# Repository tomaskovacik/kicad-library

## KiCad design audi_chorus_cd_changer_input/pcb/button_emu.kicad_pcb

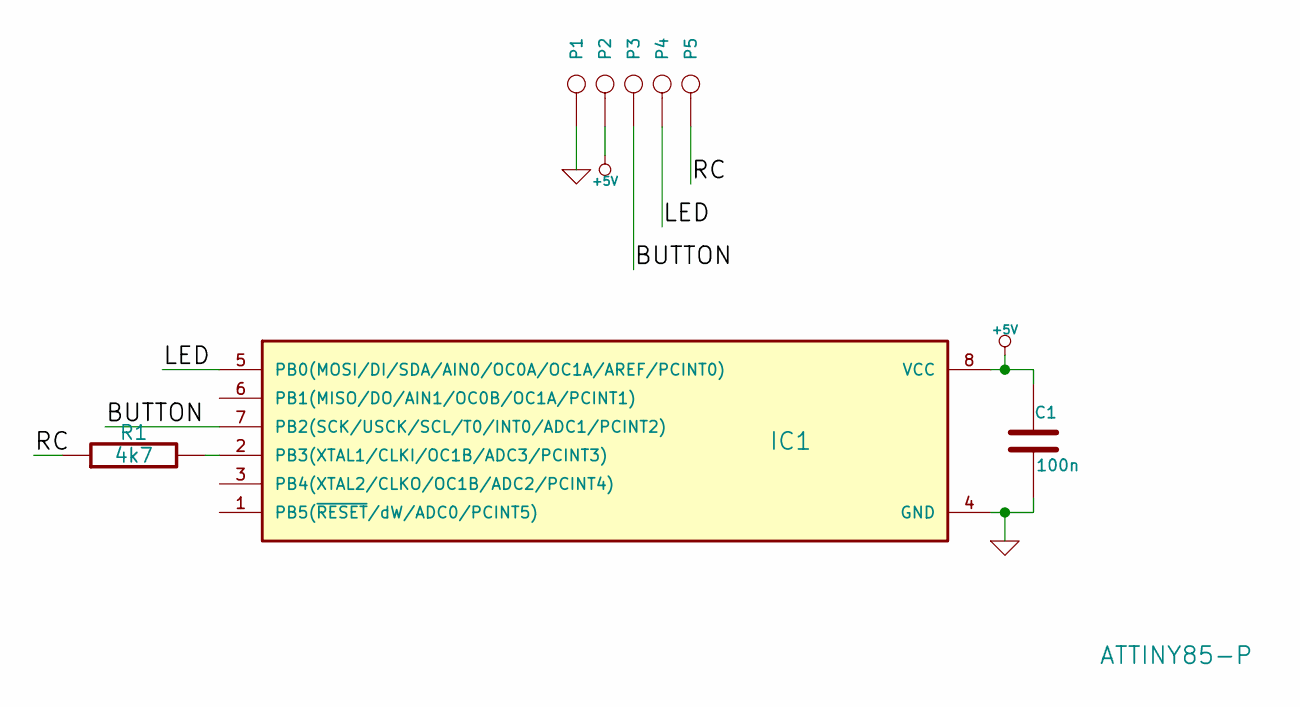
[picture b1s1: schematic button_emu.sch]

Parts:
C1: 100n
IC1: ATTINY85-P; DIP8
P1, P2, P3, P4, P5: CONN_1
R1: 4k7

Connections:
+5V: C1.1, IC1.8 (VCC), P2.1
/BUTTON: IC1.7 (PB2(SCK/USCK/SCL/T0/INT0/ADC1/PCINT2)), P3.1
/LED: IC1.5 (PB0(MOSI/DI/SDA/AIN0/OC0A/OC1A/AREF/PCI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), P4.1
/RC: P5.1, R1.1
GND: C1.2, IC1.4 (GND), P1.1
unnamed: IC1.2 (PB3(XTAL1/CLKI/OC1B/ADC3/PCINT3)), R1.2

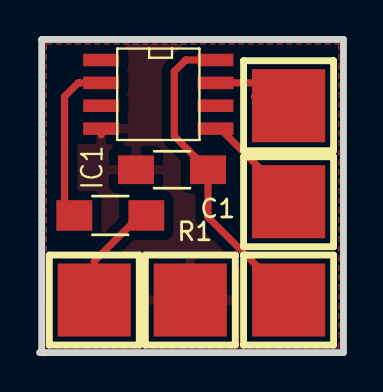
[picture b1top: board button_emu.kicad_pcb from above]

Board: 2 copper layers, 16.9 x 17.4 mm, 8 parts (0 on the bottom side), 6 nets.

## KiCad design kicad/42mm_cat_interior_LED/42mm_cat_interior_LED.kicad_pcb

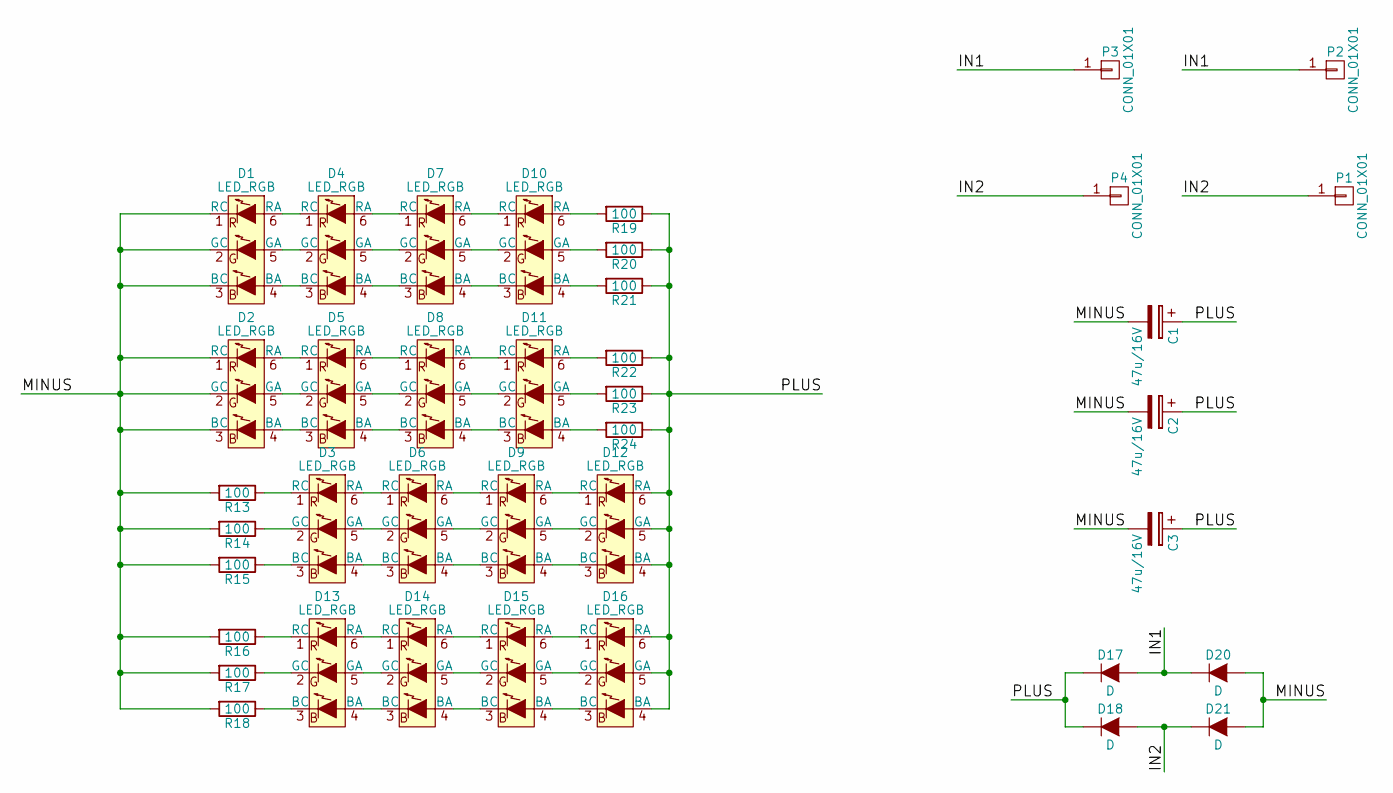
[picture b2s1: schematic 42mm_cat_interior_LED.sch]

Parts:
C1, C2, C3: 47u/16V; TantalC_SizeD_EIA-7343
D1, D2, D3, D4, D5, D6, D7, D8, D9, D10, D11, D12, D13, D14, D15, D16: LED_RGB; 5050_LED
D17, D18, D20, D21: D; DO-214AA
P1, P2, P3, P4: CONN_01X01; 1Pin
R13, R14, R15, R16, R17, R18, R19, R20, R21, R22, R23, R24: 100; R_1206

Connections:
/IN1: D17.2 (A), D20.1 (K), P2.1, P3.1
/IN2: D18.2 (A), D21.1 (K), P1.1, P4.1
/MINUS: C1.2, C2.2, C3.2, D1.1 (RC), D1.2 (GC), D1.3 (BC), D2.1 (RC), D2.2 (GC), D2.3 (BC), D20.2 (A), D21.2 (A), R13.2, R14.2, R15.2, R16.2, R17.2, R18.2
/PLUS: C1.1, C2.1, C3.1, D12.4 (BA), D12.5 (GA), D12.6 (RA), D16.4 (BA), D16.5 (GA), D16.6 (RA), D17.1 (K), D18.1 (K), R19.1, R20.1, R21.1, R22.1, R23.1, R24.1
unnamed: D1.4 (BA), D4.3 (BC)
unnamed: D1.5 (GA), D4.2 (GC)
unnamed: D1.6 (RA), D4.1 (RC)
unnamed: D2.4 (BA), D5.3 (BC)
unnamed: D2.5 (GA), D5.2 (GC)
unnamed: D2.6 (RA), D5.1 (RC)
unnamed: D3.1 (RC), R13.1
unnamed: D3.2 (GC), R14.1
unnamed: D3.3 (BC), R15.1
unnamed: D3.4 (BA), D6.3 (BC)
unnamed: D3.5 (GA), D6.2 (GC)
unnamed: D3.6 (RA), D6.1 (RC)
unnamed: D4.4 (BA), D7.3 (BC)
unnamed: D4.5 (GA), D7.2 (GC)
unnamed: D4.6 (RA), D7.1 (RC)
unnamed: D5.4 (BA), D8.3 (BC)
unnamed: D5.5 (GA), D8.2 (GC)
unnamed: D5.6 (RA), D8.1 (RC)
unnamed: D6.4 (BA), D9.3 (BC)
unnamed: D6.5 (GA), D9.2 (GC)
unnamed: D6.6 (RA), D9.1 (RC)
unnamed: D7.6 (RA), D10.1 (RC)
unnamed: D7.5 (GA), D10.2 (GC)
unnamed: D7.4 (BA), D10.3 (BC)
unnamed: D10.4 (BA), R21.2
unnamed: D10.5 (GA), R20.2
unnamed: D10.6 (RA), R19.2
unnamed: D8.6 (RA), D11.1 (RC)
unnamed: D8.5 (GA), D11.2 (GC)
unnamed: D8.4 (BA), D11.3 (BC)
unnamed: D11.4 (BA), R24.2
unnamed: D11.5 (GA), R23.2
unnamed: D11.6 (RA), R22.2
unnamed: D9.6 (RA), D12.1 (RC)
unnamed: D9.5 (GA), D12.2 (GC)
unnamed: D9.4 (BA), D12.3 (BC)
unnamed: D13.1 (RC), R16.1
unnamed: D13.2 (GC), R17.1
unnamed: D13.3 (BC), R18.1
unnamed: D13.4 (BA), D14.3 (BC)
unnamed: D13.5 (GA), D14.2 (GC)
unnamed: D13.6 (RA), D14.1 (RC)
unnamed: D14.4 (BA), D15.3 (BC)
unnamed: D14.5 (GA), D15.2 (GC)
unnamed: D14.6 (RA), D15.1 (RC)
unnamed: D15.4 (BA), D16.3 (BC)
unnamed: D15.5 (GA), D16.2 (GC)
unnamed: D15.6 (RA), D16.1 (RC)

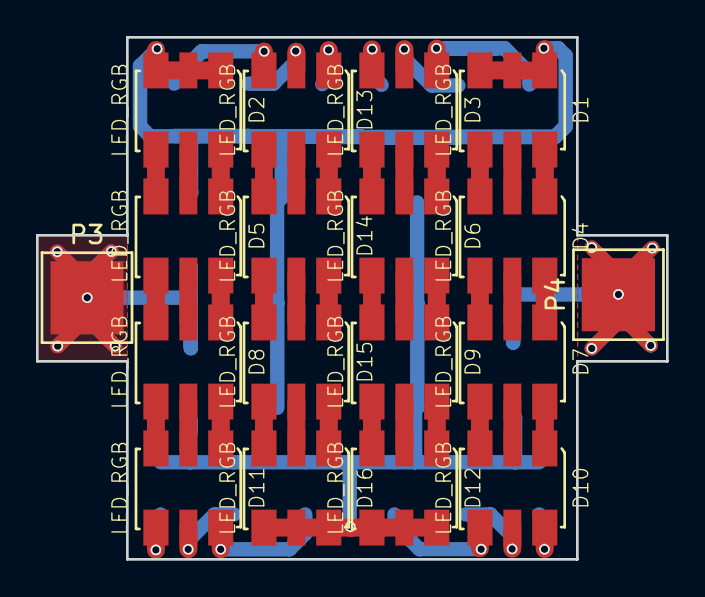
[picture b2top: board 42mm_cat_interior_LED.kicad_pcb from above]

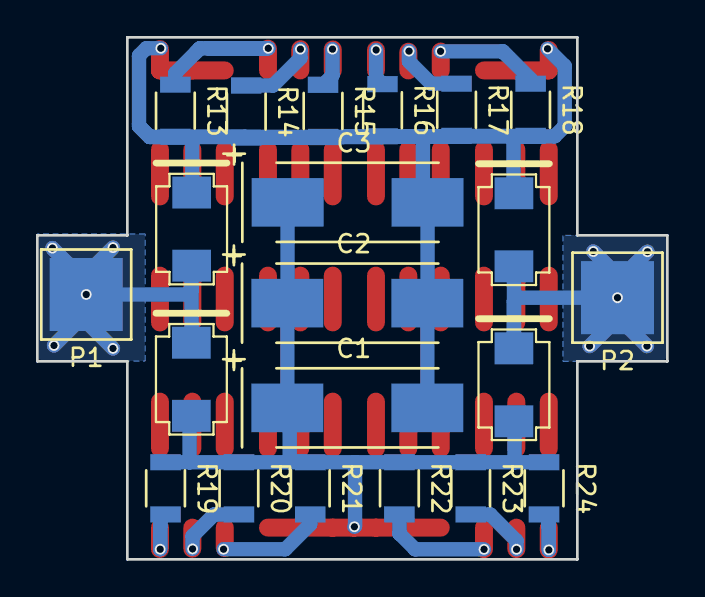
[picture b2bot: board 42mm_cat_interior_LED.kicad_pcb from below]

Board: 2 copper layers, 35.0 x 29.0 mm, 39 parts (21 on the bottom side), 52 nets.

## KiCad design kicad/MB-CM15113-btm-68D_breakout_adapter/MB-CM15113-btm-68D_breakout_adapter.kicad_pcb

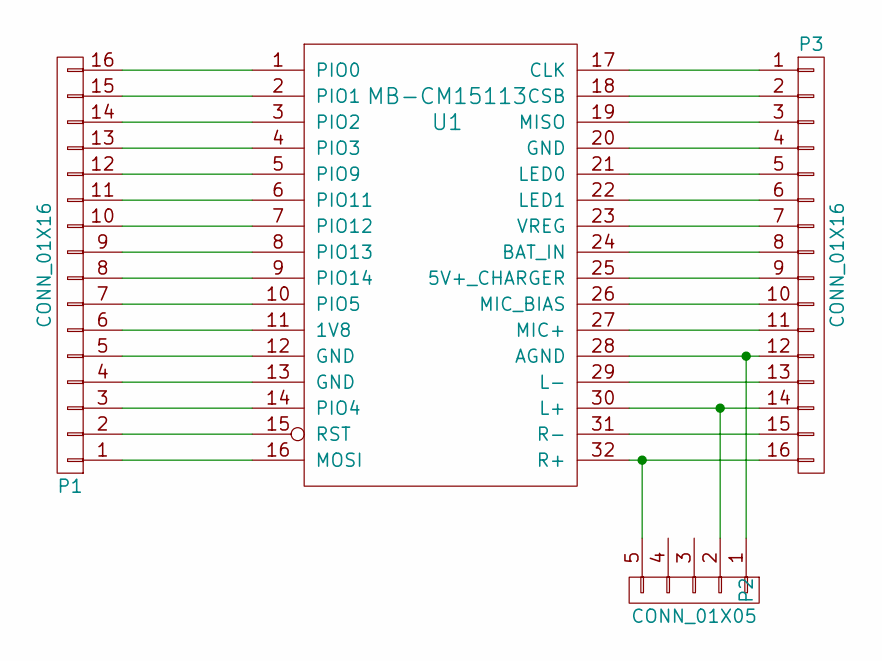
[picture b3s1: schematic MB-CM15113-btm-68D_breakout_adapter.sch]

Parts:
P1, P3: CONN_01X16; Pin_Header_Straight_1x16
P2: CONN_01X05; 3.5mm_stereo_jack_PJ320B
U1: MB-CM15113

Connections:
unnamed: P1.1, U1.16 (MOSI)
unnamed: P1.2, U1.15 (RST)
unnamed: P1.3, U1.14 (PIO4)
unnamed: P1.4, U1.13 (GND)
unnamed: P1.5, U1.12 (GND)
unnamed: P1.6, U1.11 (1V8)
unnamed: P1.7, U1.10 (PIO5)
unnamed: P1.8, U1.9 (PIO14)
unnamed: P1.9, U1.8 (PIO13)
unnamed: P1.10, U1.7 (PIO12)
unnamed: P1.11, U1.6 (PIO11)
unnamed: P1.12, U1.5 (PIO9)
unnamed: P1.13, U1.4 (PIO3)
unnamed: P1.14, U1.3 (PIO2)
unnamed: P1.15, U1.2 (PIO1)
unnamed: P1.16, U1.1 (PIO0)
unnamed: P2.1, P3.12, U1.28 (AGND)
unnamed: P2.2, P3.14, U1.30 (L+)
unnamed: P2.5, P3.16, U1.32 (R+)
unnamed: P3.1, U1.17 (CLK)
unnamed: P3.2, U1.18 (CSB)
unnamed: P3.3, U1.19 (MISO)
unnamed: P3.4, U1.20 (GND)
unnamed: P3.5, U1.21 (LED0)
unnamed: P3.6, U1.22 (LED1)
unnamed: P3.7, U1.23 (VREG)
unnamed: P3.8, U1.24 (BAT_IN)
unnamed: P3.9, U1.25 (5V+_CHARGER)
unnamed: P3.10, U1.26 (MIC_BIAS)
unnamed: P3.11, U1.27 (MIC+)
unnamed: P3.13, U1.29 (L-)
unnamed: P3.15, U1.31 (R-)

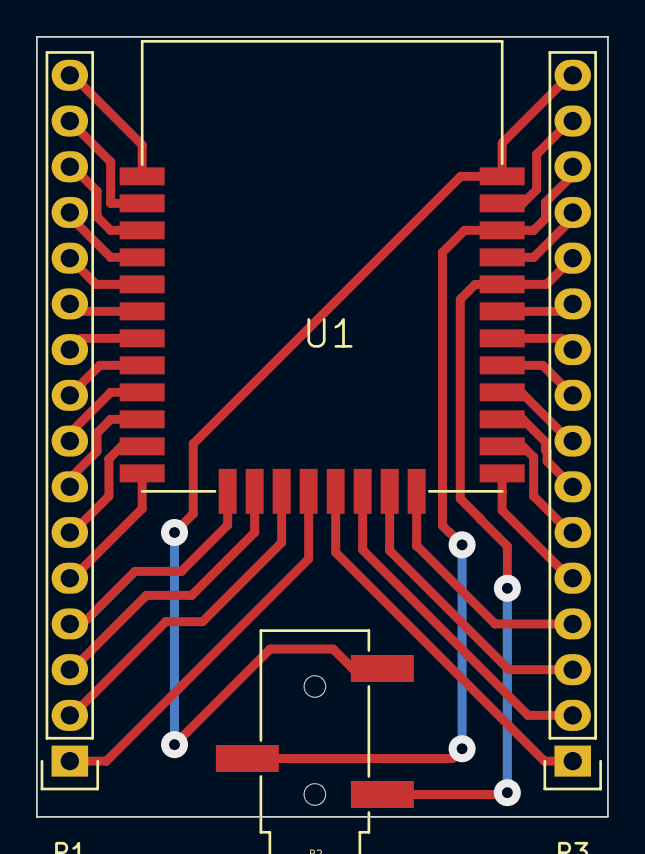
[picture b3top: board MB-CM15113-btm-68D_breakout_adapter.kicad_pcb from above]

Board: 2 copper layers, 31.7 x 43.3 mm, 4 parts (0 on the bottom side), 32 nets.

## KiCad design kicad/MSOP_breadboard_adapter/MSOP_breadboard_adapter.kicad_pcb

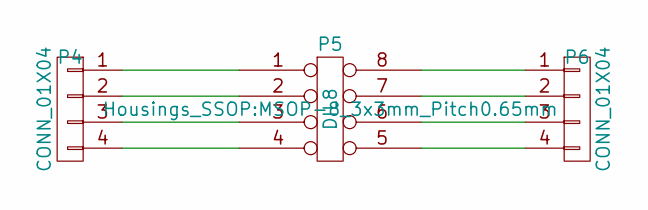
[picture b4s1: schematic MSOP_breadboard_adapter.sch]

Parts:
P4, P6: CONN_01X04; Pin_Header_Straight_1x04
P5: DIL8; MSOP-8_3x3mm_Pitch0.65mm

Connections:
unnamed: P4.1, P5.1
unnamed: P4.2, P5.2
unnamed: P4.3, P5.3
unnamed: P4.4, P5.4
unnamed: P5.5, P6.4
unnamed: P5.6, P6.3
unnamed: P5.7, P6.2
unnamed: P5.8, P6.1

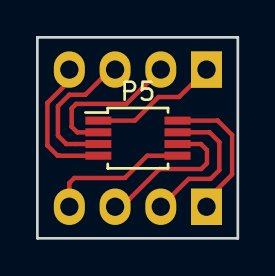
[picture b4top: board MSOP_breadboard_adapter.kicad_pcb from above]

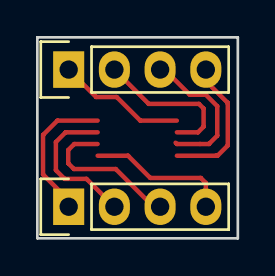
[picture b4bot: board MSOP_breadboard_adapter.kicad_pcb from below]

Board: 2 copper layers, 11.1 x 11.2 mm, 3 parts (2 on the bottom side), 8 nets.

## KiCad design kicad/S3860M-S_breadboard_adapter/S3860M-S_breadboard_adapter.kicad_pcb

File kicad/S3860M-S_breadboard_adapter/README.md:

breadboard adapters for these adapters can be purchase at tindie:

BLK-MD-SPK-B https://www.tindie.com/products/tomaskovacik/breadboard-adapter-for-blk-md-spk-b/

XS3886 / S3860M-s https://www.tindie.com/products/tomaskovacik/breadboard-adapter-for-s3860m-s-sx3868/

SOYO-BT24G03 https://www.tindie.com/products/tomaskovacik/breadboard-adapter-for-soyo-bt24g03-bt-module/

F-3188 https://www.tindie.com/products/tomaskovacik/breadboard-adapter-for-f-3188-csr8645-module/

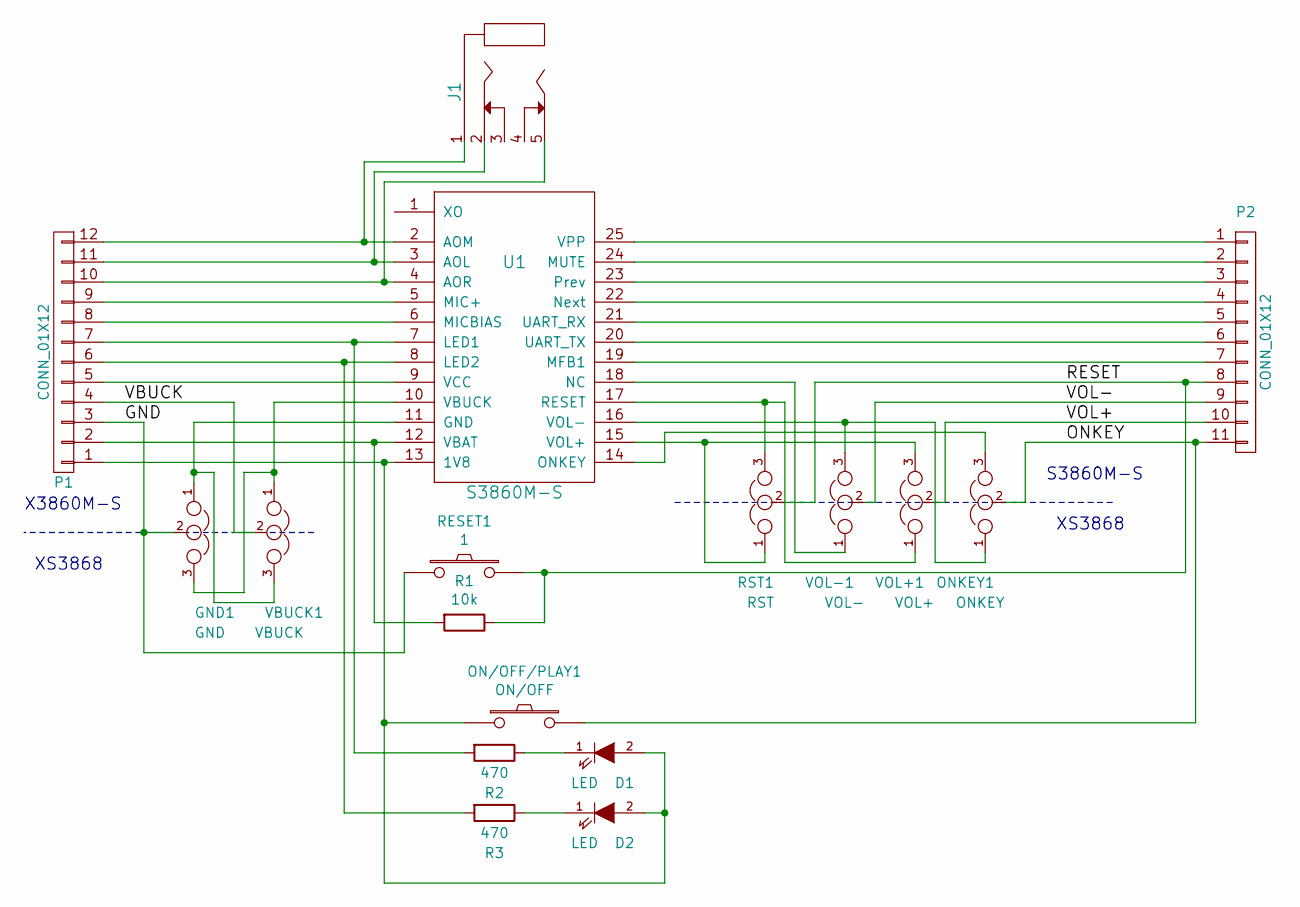
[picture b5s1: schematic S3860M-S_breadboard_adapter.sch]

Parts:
D1, D2: LED; LED-1206
GND1: GND; S_JUMPER_3
J1: SCJ368R1NUS0B00G; 3.5mm_stereo_jack_PJ320B
ON/OFF/PLAY1: ON/OFF; SW_SPST_FSMSM
ONKEY1: ONKEY; S_JUMPER_3
P1: CONN_01X12; Pin_Header_Straight_1x12
P2: CONN_01X12; Pin_Header_Straight_1x11
R1: 10k; R_0805_HandSoldering
R2, R3: 470; R_0805_HandSoldering
RESET1: 1; SW_SPST_FSMSM
RST1: RST; S_JUMPER_3
U1: S3860M-S; XS3868
VBUCK1: VBUCK; S_JUMPER_3
VOL+1: VOL+; S_JUMPER_3
VOL-1: VOL-; S_JUMPER_3

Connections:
/GND: GND1.2, P1.3, RESET1.1
/ONKEY: ON/OFF/PLAY1.2, ONKEY1.2, P2.11
/RESET: P2.8, R1.1, RESET1.2, RST1.2
/VBUCK: P1.4, VBUCK1.2
/VOL+: P2.10, VOL+1.2
/VOL-: P2.9, VOL-1.2
unnamed: D1.1 (K), R2.1
unnamed: D1.2 (A), D2.2 (A), ON/OFF/PLAY1.1, P1.1, U1.13 (1V8)
unnamed: D2.1 (K), R3.1
unnamed: GND1.1, U1.11 (GND), VBUCK1.3
unnamed: GND1.3, U1.10 (VBUCK), VBUCK1.1
unnamed: J1.1, P1.12, U1.2 (AOM)
unnamed: J1.2, P1.11, U1.3 (AOL)
unnamed: J1.5, P1.10, U1.4 (AOR)
unnamed: ONKEY1.1, U1.16 (VOL-), VOL-1.3
unnamed: ONKEY1.3, U1.14 (ONKEY)
unnamed: P1.2, R1.2, U1.12 (VBAT)
unnamed: P1.5, U1.9 (VCC)
unnamed: P1.6, R3.2, U1.8 (LED2)
unnamed: P1.7, R2.2, U1.7 (LED1)
unnamed: P1.8, U1.6 (MICBIAS)
unnamed: P1.9, U1.5 (MIC+)
unnamed: P2.1, U1.25 (VPP)
unnamed: P2.2, U1.24 (MUTE)
unnamed: P2.3, U1.23 (Prev)
unnamed: P2.4, U1.22 (Next)
unnamed: P2.5, U1.21 (UART_RX)
unnamed: P2.6, U1.20 (UART_TX)
unnamed: P2.7, U1.19 (MFB1)
unnamed: RST1.1, U1.15 (VOL+), VOL+1.3
unnamed: RST1.3, U1.17 (RESET), VOL+1.1
unnamed: U1.18 (NC), VOL-1.1

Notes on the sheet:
XS3868
S3860M-S
X3860M-S

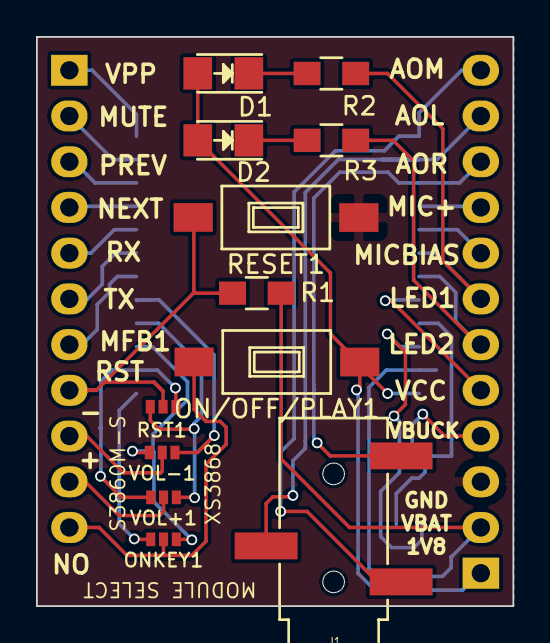
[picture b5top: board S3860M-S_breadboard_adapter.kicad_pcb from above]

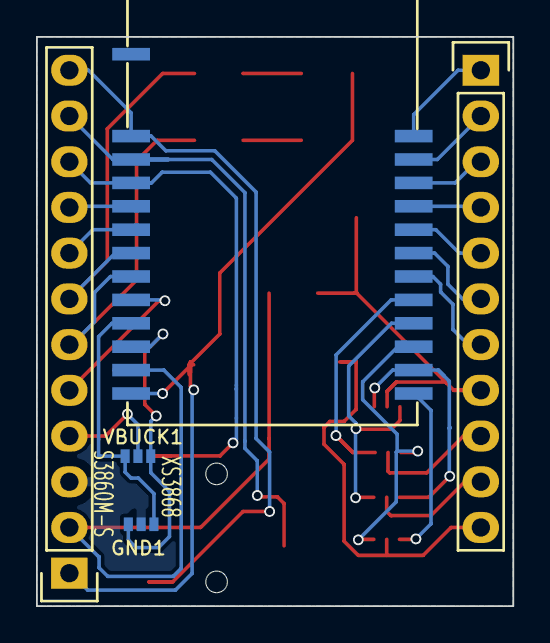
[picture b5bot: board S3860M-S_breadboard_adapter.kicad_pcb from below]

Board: 2 copper layers, 26.5 x 31.6 mm, 17 parts (5 on the bottom side), 32 nets.

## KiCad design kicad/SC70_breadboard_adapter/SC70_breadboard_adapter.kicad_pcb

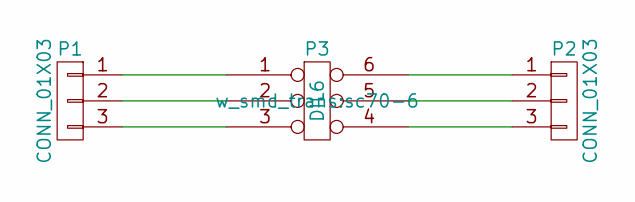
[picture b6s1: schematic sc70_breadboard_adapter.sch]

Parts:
P1, P2: CONN_01X03; Pin_Header_Straight_1x03
P3: DIL6; sc70-6

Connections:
unnamed: P1.1, P3.1
unnamed: P1.2, P3.2
unnamed: P1.3, P3.3
unnamed: P2.1, P3.6
unnamed: P2.2, P3.5
unnamed: P2.3, P3.4

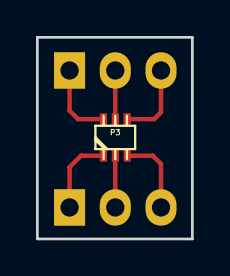
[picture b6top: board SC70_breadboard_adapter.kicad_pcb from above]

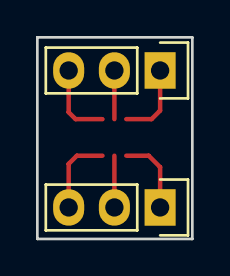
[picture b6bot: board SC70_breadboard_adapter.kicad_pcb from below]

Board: 2 copper layers, 8.6 x 11.2 mm, 3 parts (2 on the bottom side), 6 nets.

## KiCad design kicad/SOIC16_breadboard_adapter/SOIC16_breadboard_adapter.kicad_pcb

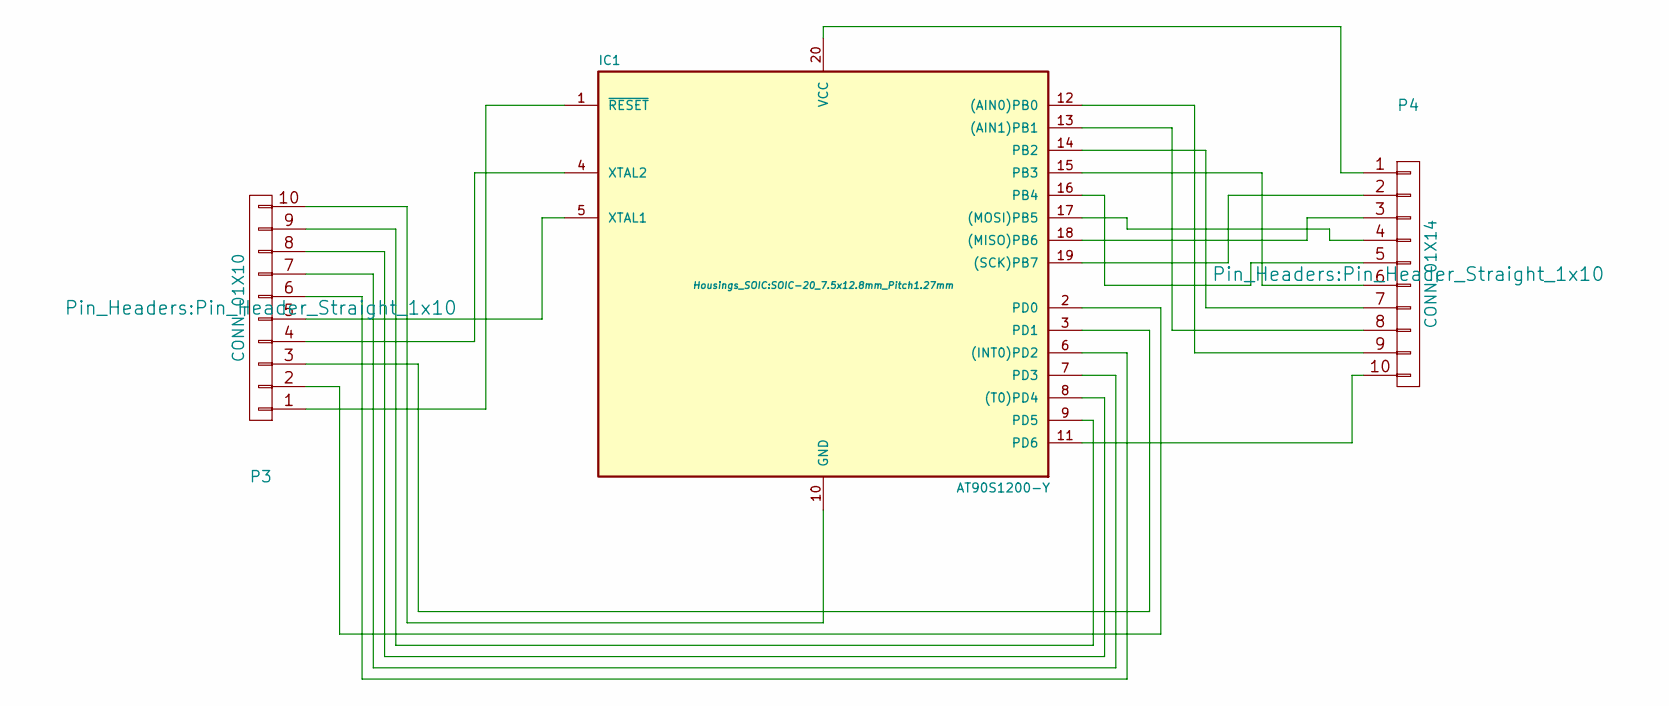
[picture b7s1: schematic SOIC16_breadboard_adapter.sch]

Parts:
IC1: AT90S1200-Y; SOIC-20_7.5x12.8mm_Pitch1.27mm
P3: CONN_01X10; Pin_Header_Straight_1x10
P4: CONN_01X14; Pin_Header_Straight_1x10

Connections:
unnamed: IC1.1 (~RESET), P3.1
unnamed: IC1.2 (PD0), P3.2
unnamed: IC1.3 (PD1), P3.3
unnamed: IC1.4 (XTAL2), P3.4
unnamed: IC1.5 (XTAL1), P3.5
unnamed: IC1.6 ((INT0)PD2), P3.6
unnamed: IC1.7 (PD3), P3.7
unnamed: IC1.8 ((T0)PD4), P3.8
unnamed: IC1.9 (PD5), P3.9
unnamed: IC1.10 (GND), P3.10
unnamed: IC1.11 (PD6), P4.10
unnamed: IC1.12 ((AIN0)PB0), P4.9
unnamed: IC1.13 ((AIN1)PB1), P4.8
unnamed: IC1.14 (PB2), P4.7
unnamed: IC1.15 (PB3), P4.6
unnamed: IC1.16 (PB4), P4.5
unnamed: IC1.17 ((MOSI)PB5), P4.4
unnamed: IC1.18 ((MISO)PB6), P4.3
unnamed: IC1.19 ((SCK)PB7), P4.2
unnamed: IC1.20 (VCC), P4.1

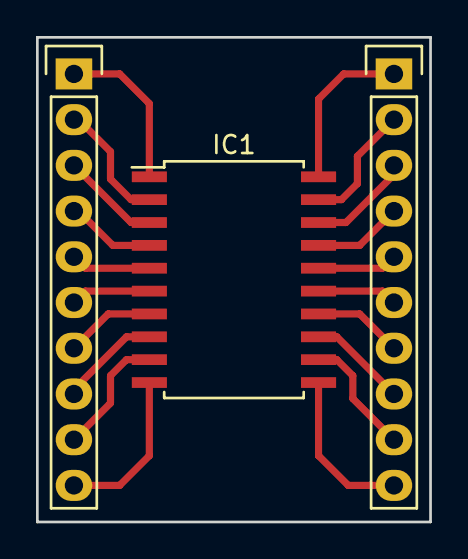
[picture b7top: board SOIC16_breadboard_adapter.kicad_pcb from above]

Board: 2 copper layers, 21.8 x 26.9 mm, 3 parts (0 on the bottom side), 20 nets.
